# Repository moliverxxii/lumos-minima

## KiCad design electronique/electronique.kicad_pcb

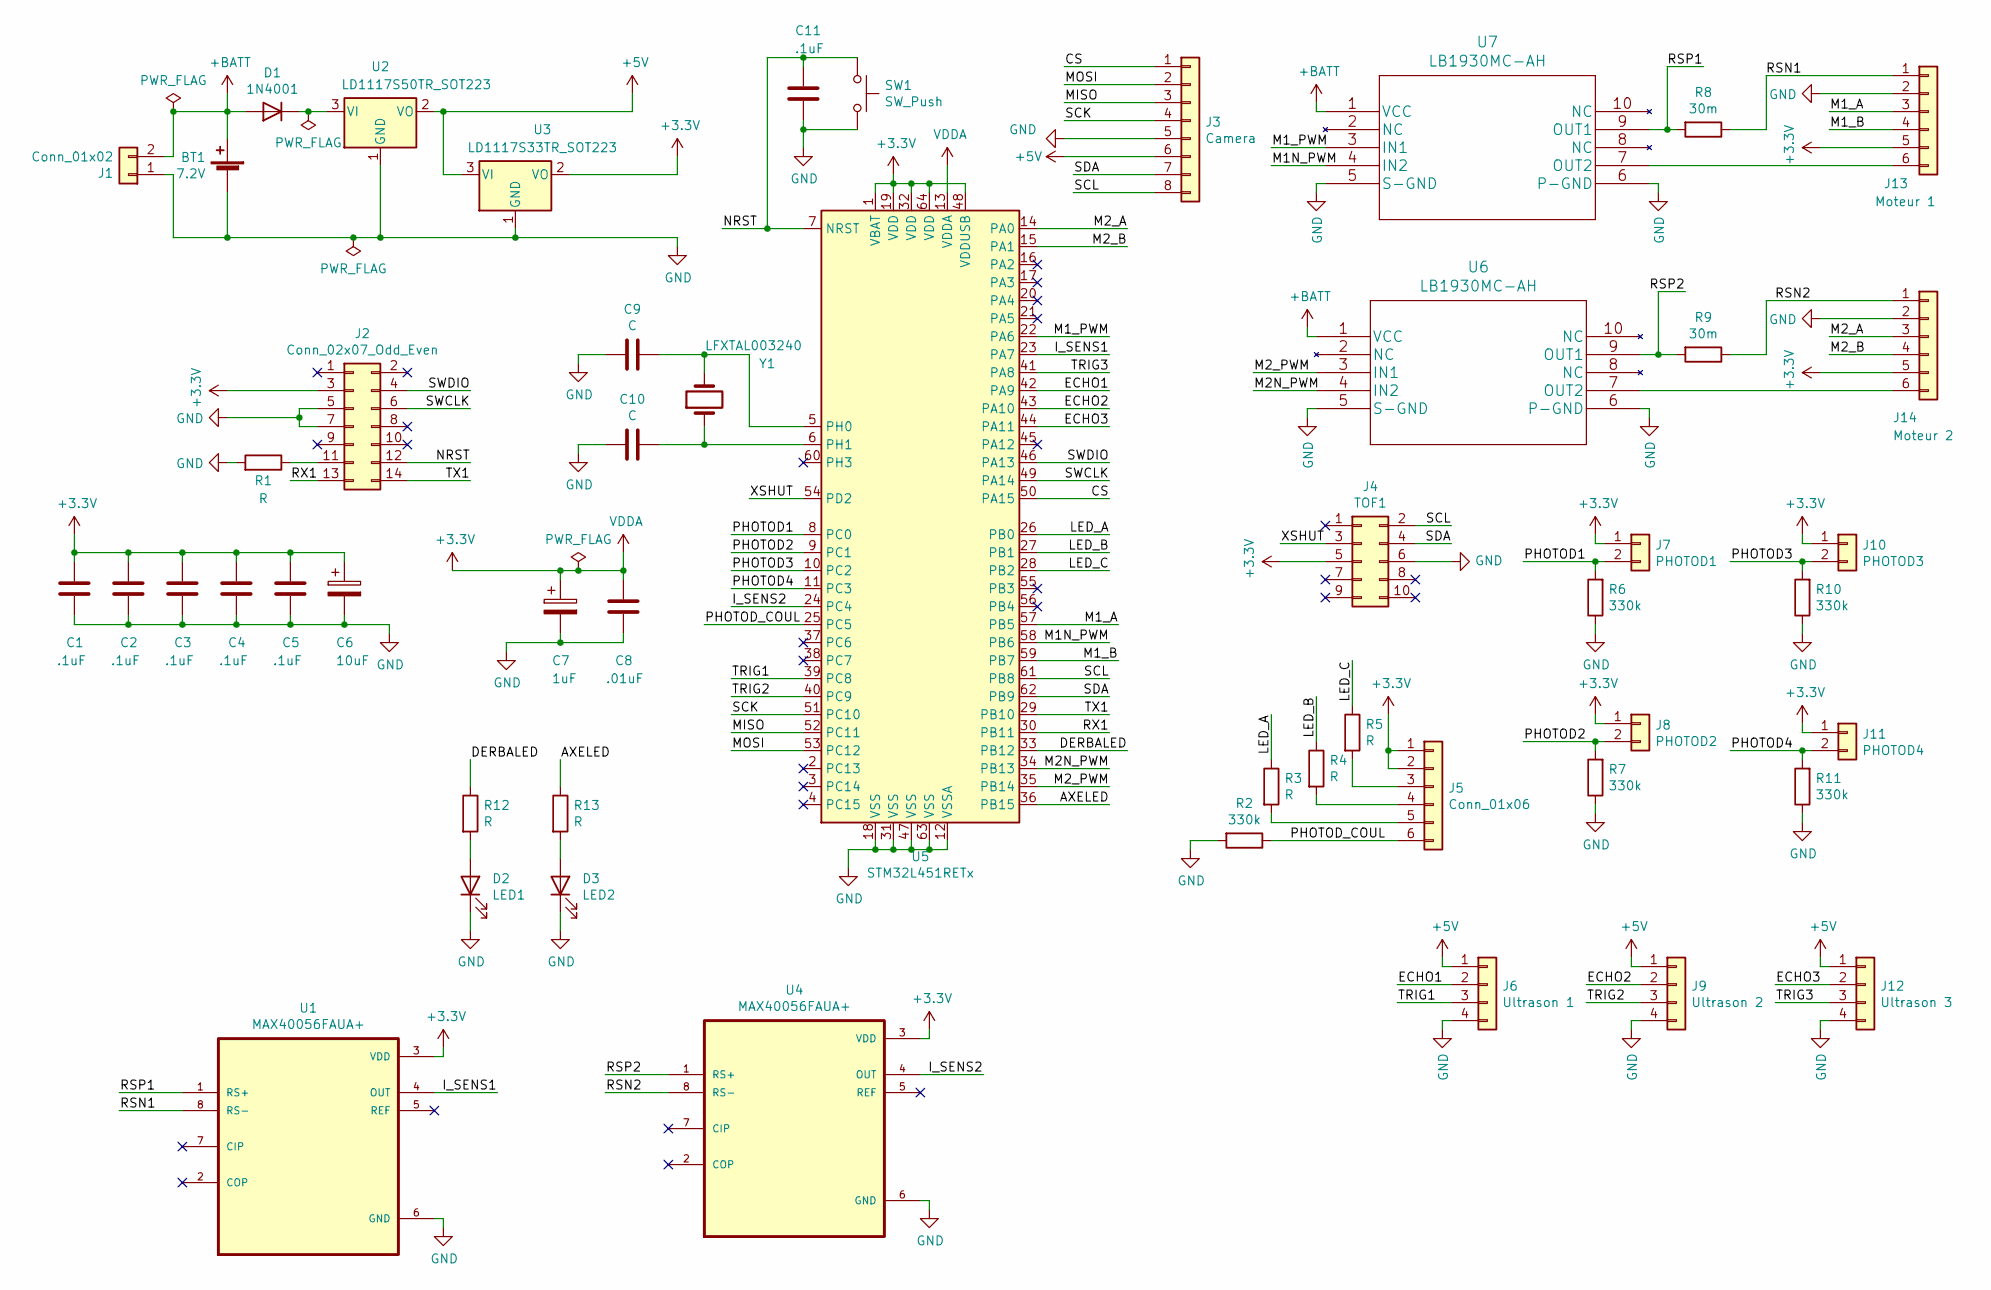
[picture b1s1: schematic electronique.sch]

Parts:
BT1: 7.2V; PinHeader_2x01_P2.54mm_Vertical
C1, C2, C3, C4, C5, C11: .1uF; C_0805_2012Metric_Pad1.18x1.45mm_HandSolder
C6: 10uF; CP_EIA-2012-12_Kemet-R_Pad1.30x1.05mm_HandSolder
C7: 1uF; CP_EIA-2012-12_Kemet-R_Pad1.30x1.05mm_HandSolder
C8: .01uF; C_0805_2012Metric_Pad1.18x1.45mm_HandSolder
C9, C10: C; C_0805_2012Metric_Pad1.18x1.45mm_HandSolder
D1: 1N4001; D_DO-41_SOD81_P10.16mm_Horizontal
D2: LED1; LED_0805_2012Metric_Pad1.15x1.40mm_HandSolder
D3: LED2; LED_0805_2012Metric_Pad1.15x1.40mm_HandSolder
J1: Conn_01x02; JST_PH_B2B-PH-K_1x02_P2.00mm_Vertical
J2: Conn_02x07_Odd_Even; SAMTEC_FTSH-107-01-L-DV-K-A
J3: Camera; PinHeader_1x08_P2.54mm_Vertical
J4: TOF1; PinHeader_2x05_P2.54mm_Vertical
J5: Conn_01x06; PinHeader_1x06_P2.54mm_Vertical
J6: Ultrason 1; PinHeader_1x04_P2.54mm_Vertical
J7: PHOTOD1; JST_PH_B2B-PH-K_1x02_P2.00mm_Vertical
J8: PHOTOD2; JST_PH_B2B-PH-K_1x02_P2.00mm_Vertical
J9: Ultrason 2; PinHeader_1x04_P2.54mm_Vertical
J10: PHOTOD3; JST_PH_B2B-PH-K_1x02_P2.00mm_Vertical
J11: PHOTOD4; JST_PH_B2B-PH-K_1x02_P2.00mm_Vertical
J12: Ultrason 3; PinHeader_1x04_P2.54mm_Vertical
J13: Moteur 1; JST_PH_B6B-PH-K_1x06_P2.00mm_Vertical
J14: Moteur 2; JST_PH_B6B-PH-K_1x06_P2.00mm_Vertical
R1, R3, R4, R5, R12, R13: R; R_0805_2012Metric_Pad1.20x1.40mm_HandSolder
R2, R6, R7, R10, R11: 330k; R_0805_2012Metric_Pad1.20x1.40mm_HandSolder
R8, R9: 30m; R_1206_3216Metric_Pad1.30x1.75mm_HandSolder
SW1: SW_Push; SW_PUSH_6mm
U1, U4: MAX40056FAUA+; MSOP-8_3x3mm_P0.65mm
U2: LD1117S50TR_SOT223; SOT-223-3_TabPin2
U3: LD1117S33TR_SOT223; SOT-223-3_TabPin2
U5: STM32L451RETx; LQFP-64_10x10mm_P0.5mm
U6, U7: LB1930MC-AH
Y1: LFXTAL003240; HC494H

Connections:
+3V3: C1.1, C2.1, C3.1, C4.1, C5.1, C6.1, C7.1, C8.1, J2.3, J4.5, J5.1, J5.2, J7.1, J8.1, J10.1, J11.1, J13.5, J14.5, U1.3 (VDD), U3.2 (VO), U4.3 (VDD), U5.1 (VBAT), U5.13 (VDDA), U5.19 (VDD), U5.32 (VDD), U5.48 (VDDUSB), U5.64 (VDD)
+5V: J3.6, J6.1, J9.1, J12.1, U2.2 (VO), U3.3 (VI)
+BATT: BT1.1 (+), D1.2 (A), J1.2, U6.1 (VCC), U7.1 (VCC)
/AXELED: R13.1, U5.36 (PB15)
/CS: J3.1, U5.50 (PA15)
/DERBALED: R12.1, U5.33 (PB12)
/ECHO1: J6.2, U5.42 (PA9)
/ECHO2: J9.2, U5.43 (PA10)
/ECHO3: J12.2, U5.44 (PA11)
/I_SENS1: U1.4 (OUT), U5.23 (PA7)
/I_SENS2: U4.4 (OUT), U5.24 (PC4)
/LED_A: R3.1, U5.26 (PB0)
/LED_B: R4.1, U5.27 (PB1)
/LED_C: R5.1, U5.28 (PB2)
/M1N_PWM: U5.58 (PB6), U7.4 (IN2)
/M1_A: J13.3, U5.57 (PB5)
/M1_B: J13.4, U5.59 (PB7)
/M1_PWM: U5.22 (PA6), U7.3 (IN1)
/M2N_PWM: U5.34 (PB13), U6.4 (IN2)
/M2_A: J14.3, U5.14 (PA0)
/M2_B: J14.4, U5.15 (PA1)
/M2_PWM: U5.35 (PB14), U6.3 (IN1)
/MISO: J3.3, U5.52 (PC11)
/MOSI: J3.2, U5.53 (PC12)
/NRST: C11.1, J2.12, SW1.1, U5.7 (NRST)
/PHOTOD1: J7.2, R6.2, U5.8 (PC0)
/PHOTOD2: J8.2, R7.2, U5.9 (PC1)
/PHOTOD3: J10.2, R10.2, U5.10 (PC2)
/PHOTOD4: J11.2, R11.2, U5.11 (PC3)
/PHOTOD_COUL: J5.6, R2.1, U5.25 (PC5)
/RSN1: J13.1, R8.1, U1.8 (RS-)
/RSN2: J14.1, R9.1, U4.8 (RS-)
/RSP1: R8.2, U1.1 (RS+), U7.9 (OUT1)
/RSP2: R9.2, U4.1 (RS+), U6.9 (OUT1)
/RX1: J2.13, U5.30 (PB11)
/SCK: J3.4, U5.51 (PC10)
/SCL: J3.8, J4.2, U5.61 (PB8)
/SDA: J3.7, J4.4, U5.62 (PB9)
/SWCLK: J2.6, U5.49 (PA14)
/SWDIO: J2.4, U5.46 (PA13)
/TRIG1: J6.3, U5.39 (PC8)
/TRIG2: J9.3, U5.40 (PC9)
/TRIG3: J12.3, U5.41 (PA8)
/TX1: J2.14, U5.29 (PB10)
/XSHUT: J4.3, U5.54 (PD2)
GND: BT1.2 (-), C1.2, C2.2, C3.2, C4.2, C5.2, C6.2, C7.2, C8.2, C9.1, C10.2, C11.2, D2.1 (K), D3.1 (K), J1.1, J2.5, J2.7, J3.5, J4.6, J6.4, J9.4, J12.4, J13.2, J14.2, R1.2, R2.2, R6.1, R7.1, R10.1, R11.1, SW1.2, U1.6 (GND), U2.1 (GND), U3.1 (GND), U4.6 (GND), U5.12 (VSSA), U5.18 (VSS), U5.31 (VSS), U5.47 (VSS), U5.63 (VSS), U6.5 (S-GND), U6.6 (P-GND), U7.5 (S-GND), U7.6 (P-GND)
unnamed: C9.2, U5.5 (PH0), Y1.2
unnamed: C10.1, U5.6 (PH1), Y1.1
unnamed: D1.1 (K), U2.3 (VI)
unnamed: D2.2 (A), R12.2
unnamed: D3.2 (A), R13.2
unnamed: J2.11, R1.1
unnamed: J5.3, R5.2
unnamed: J5.4, R4.2
unnamed: J5.5, R3.2
unnamed: J13.6, U7.7 (OUT2)
unnamed: J14.6, U6.7 (OUT2)

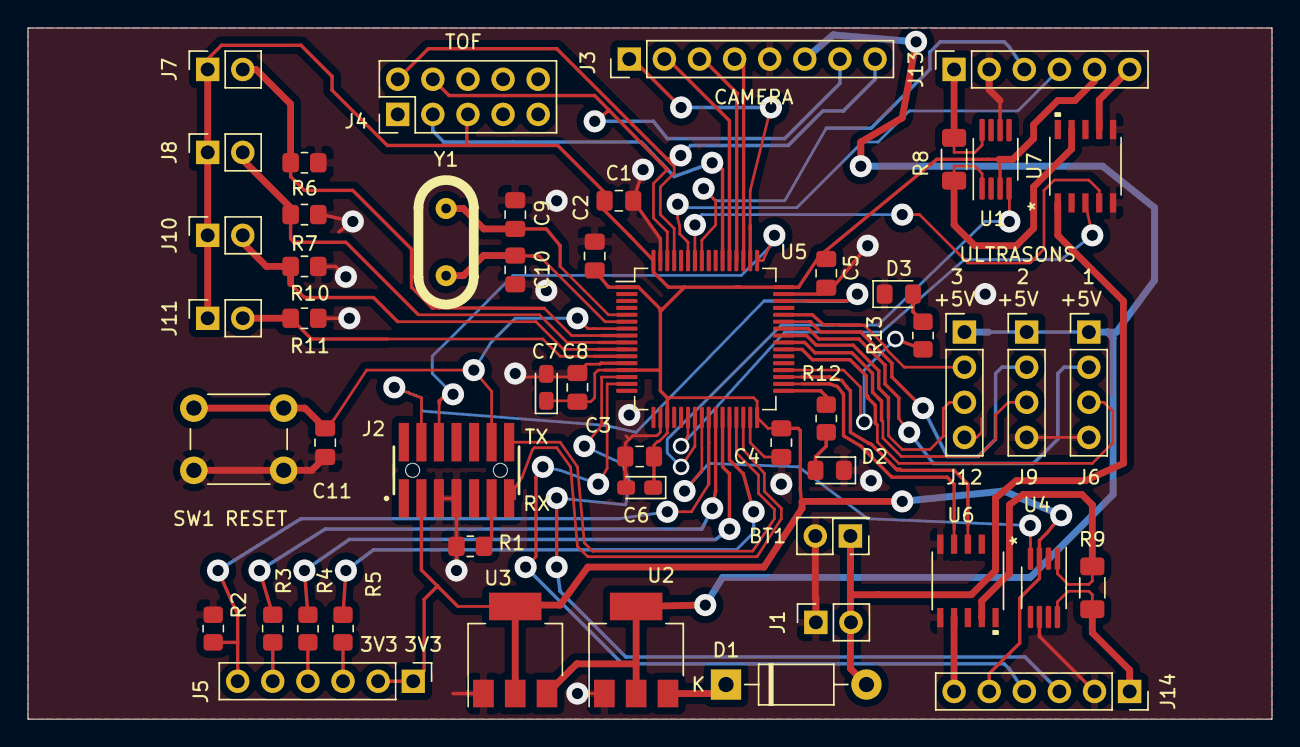
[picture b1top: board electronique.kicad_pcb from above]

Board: 2 copper layers, 90.0 x 50.0 mm, 51 parts (0 on the bottom side), 57 nets.

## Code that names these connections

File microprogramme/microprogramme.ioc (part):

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Mcu.Name=STM32L451R(C-E)Tx
Mcu.Package=LQFP64
Mcu.UserName=STM32L451RETx
PA0.Signal=S_TIM2_CH1
PA1.Signal=S_TIM2_CH2
PA10.Signal=S_TIM1_CH3
PA11.Signal=S_TIM1_CH4
PA13\ (JTMS/SWDIO).Mode=Serial_Wire
PA13\ (JTMS/SWDIO).Signal=SYS_JTMS-SWDIO
PA14\ (JTCK/SWCLK).Mode=Serial_Wire
PA14\ (JTCK/SWCLK).Signal=SYS_JTCK-SWCLK
PA15\ (JTDI).Mode=NSS_Signal_Hard_Input
PA15\ (JTDI).Signal=SPI3_NSS
PA4.Signal=SPI1_NSS
PA5.Signal=SPI1_SCK
PA6.Signal=S_TIM16_CH1
PA7.Signal=ADCx_IN12
PA8.Signal=GPIO_Output
PA9.Signal=S_TIM1_CH2
PB0.Signal=GPIO_Output
PB1.Signal=GPIO_Output
PB10.Mode=Asynchronous
PB10.Signal=USART3_TX
PB11.Mode=Asynchronous
PB11.Signal=USART3_RX
PB12.Signal=GPIO_Output
PB13.Mode=PWM Generation1 CH1 CH1N
PB13.Signal=TIM15_CH1N
PB14.Signal=S_TIM15_CH1
PB15.Signal=GPIO_Output
PB2.Signal=GPIO_Output
PB5.Mode=Encoder_mode_occur1
PB5.Signal=LPTIM1_IN1
PB6.Mode=PWM Generation1 CH1 CH1N
PB6.Signal=TIM16_CH1N
PB7.Mode=Encoder_mode_occur1
PB7.Signal=LPTIM1_IN2
PB8.Mode=I2C
PB8.Signal=I2C1_SCL
PB9.Mode=I2C
PB9.Signal=I2C1_SDA
PC0.Signal=ADCx_IN1
PC1.Signal=ADCx_IN2
PC10.Mode=Full_Duplex_Master
PC10.Signal=SPI3_SCK
PC11.Mode=Full_Duplex_Master
PC11.Signal=SPI3_MISO
PC12.Mode=Full_Duplex_Master
PC12.Signal=SPI3_MOSI
PC2.Signal=ADCx_IN3
PC3.Signal=ADCx_IN4
PC4.Signal=ADCx_IN13
PC5.Signal=ADCx_IN14
PC8.Signal=GPIO_Output
PC9.Signal=GPIO_Output
PD2.Signal=GPIO_Output
PH0-OSC_IN\ (PH0).Mode=HSE-External-Oscillator
PH0-OSC_IN\ (PH0).Signal=RCC_OSC_IN
PH1-OSC_OUT\ (PH1).Mode=HSE-External-Oscillator
PH1-OSC_OUT\ (PH1).Signal=RCC_OSC_OUT
RCC.HSE_VALUE=16000000
RCC.SYSCLKFreq_VALUE=80000000
RCC.SYSCLKSource=RCC_SYSCLKSOURCE_PLLCLK
board=custom

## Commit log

2021-09-29 Test pour le programme
2021-10-01 nouveaufichier
2021-10-01 test 1
2021-10-01 Schema ajoute.
2021-10-06 Ajoute .gitignore KiCad
2021-10-06 Schema change
2021-10-12 Nettoye
2021-10-12 Mis a jour .gitignore
2021-10-13 GPIO configure
2021-10-15 Schema mis a jour pour la seance de projet
2021-10-15 Creation du dossier fiches-techniques-annexe
2021-10-15 Configuration initiale du microcontroleur
2021-10-15 PLUS DE FICHES TECHNIQUES git add fiches-techniques-annexe!
2021-10-15 Schema/Routage presque finis
2021-10-16 Projet Test UltraSon
2021-10-20 Ajout de l'ampli de captage de courant MAX40056.
2021-10-20 Ajout de la fiche technique de MAX40056
2021-10-20 Suppression de fichier de bibliothèque qui sont vides.
2021-10-20 Ajout du manuel de reference stm32l4
2021-10-20 Changement des configurations des TIMs.
2021-10-20 Cablage preliminaire des capteurs de courant
2021-10-27 Ajout fiche technique resistances mesure de courant Vishay.
2021-10-27 Schema de concept termine, il manque les valeurs de certains condensateurs, il est possible qu'il y aie besoin de plus de condensateurs.
2021-10-27 Configuration .ioc mise a jour.
2021-10-27 PLUS DE FICHES TECHNIQUES !
2021-10-27 pcb vide
2021-10-29 Avancement du routage
2021-11-04 Example commit sur autre branche
2021-11-04 Ajout valeurs de resistances photodiodes
2021-11-04 Circuit routé attente de validation
2021-11-07 Avancement Routage
2021-11-07 Mise a jour de kicad
2021-11-11 Fin du routage
2021-11-17 Changement IOC
2021-11-17 Ajout de LEDs, reste a ajouter au circuit imprime
2021-11-18 Ajout fiche techniqu LD1117
2021-11-19 Circuit imprime a valider par technicien
2021-11-19 Idem
2021-11-19 Schema capteur de couleur
2021-11-20 Deplacement dossier capteur de couleur
2021-11-20 Moins de vias.
2021-11-20 Retrait de TesteProjet.rar
2021-11-26 ajout de vias
2021-11-30 Mise a jour CI
2021-12-03 Circuit imprimé FINAL.
2021-12-03 Electronique
2021-12-03 Capteur couleur
2021-12-03 Configuration .ioc
2021-12-03 Les fichers systeme STM32CubeIDE sont ignores

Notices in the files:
parts and their libraries:
Copyright 2021 Accelerated Designs. All rights reserved.
